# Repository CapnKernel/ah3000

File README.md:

# Raymarine/Nautech Autohelm 3000 control board

Here is a KiCad project of the schematic and layout of the Raymarine/Nautech
Autohelm 3000 control board, a late 80s/early 90s autohelm for sailboats.

These designs were captured by analysing some Autohelm 3000 boards with a
magnifying glass and a multimeter set to the "beep" continuity mode.

There are errors, use with caution.  Component sizes and positions are only approximate.

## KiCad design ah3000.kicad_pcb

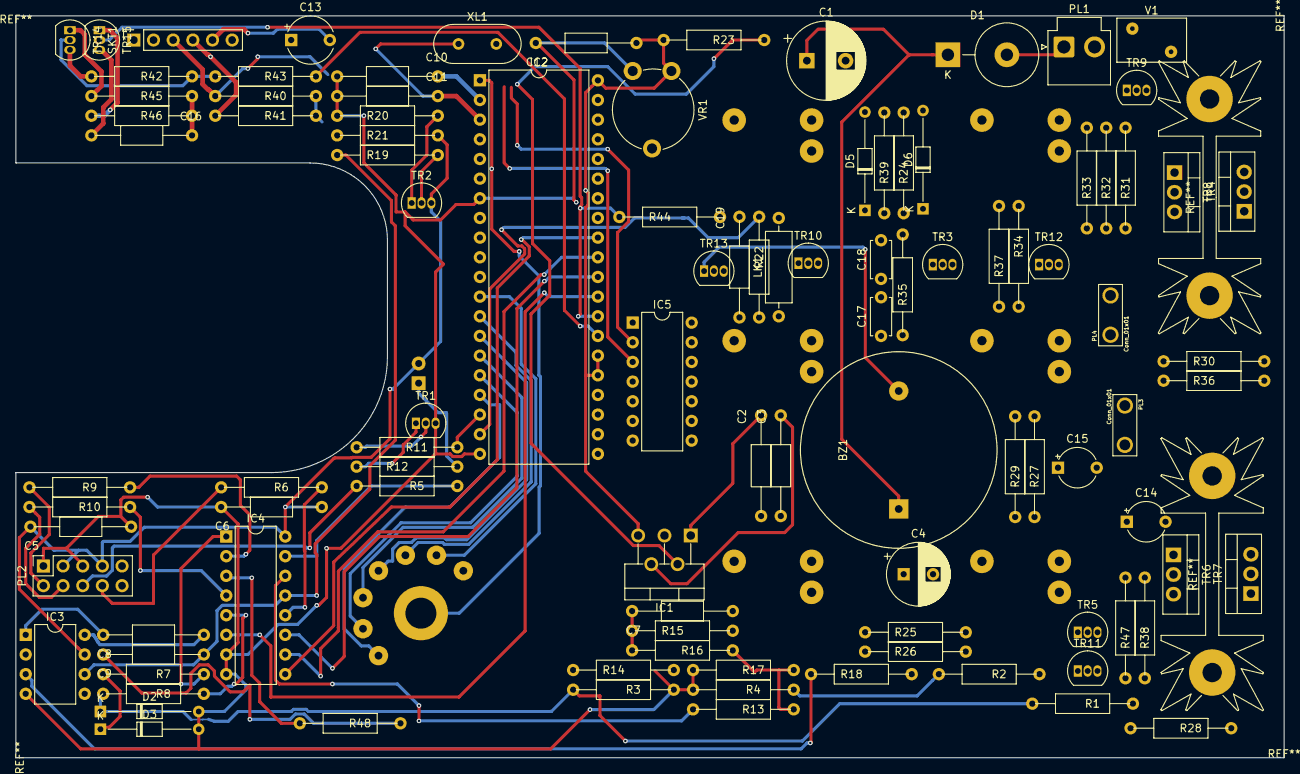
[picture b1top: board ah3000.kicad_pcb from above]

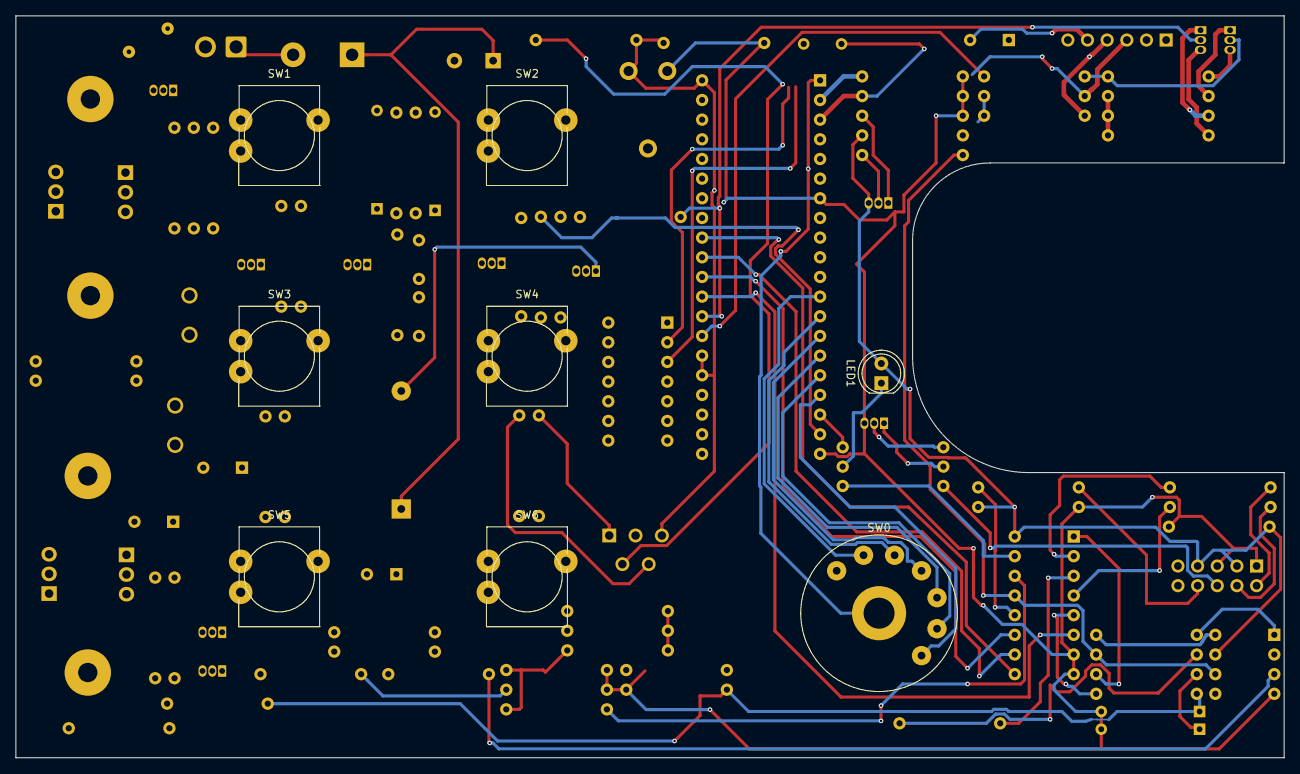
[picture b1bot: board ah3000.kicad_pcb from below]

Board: 2 copper layers, 163.8 x 95.8 mm, 110 parts (8 on the bottom side), 88 nets.

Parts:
BZ1: Buzzer; Buzzer_23x20RM15
C1: CP; CP_Radial_D10.0mm_P5.00mm
C2, C3, C5, C6, C7, C8, C9, C10, C11, C12, C16, C19: C; C_DO-41_SOD81_P12.70mm_Horizontal
C4: CP; CP_Radial_D8.0mm_P3.80mm
C13: 2u2; CP_Radial_Tantal_D6.0mm_P5.00mm
C14, C15: CP; CP_Radial_Tantal_D5.0mm_P5.00mm
C17, C18: C; C_Disc_D4.7mm_W2.5mm_P5.00mm
D1: D; D_5KPW_P7.62mm_Vertical_KathodeUp
D2, D3, D5, D6: D_ALT; D_DO-34_SOD68_P12.70mm_Horizontal
IC1: L487; TO-220-5_P3.4x3.7mm_StaggerOdd_Lead3.8mm_Vertical
IC2: Conn_02x20_Counter_Clockwise; DIP-40_W15.24mm
IC3: CA3130; DIP-8_W7.62mm
IC4: 4051; DIP-16_W7.62mm
IC5: M74HC4066B1R; DIP-14_W7.62mm
LED1: LED_ALT; LED_D5.0mm
LK1: Jumper_NC_Small; R_Axial_DIN0309_L9.0mm_D3.2mm_P12.70mm_Horizontal
PL1: Conn_01x02; JST_VH_B2P-VH-B_1x02_P3.96mm_Vertical
PL2: Conn_02x05_Counter_Clockwise; PinSocket_2x05_P2.54mm_Vertical
PL3, PL4: Conn_01x01; CONN_63824-1
R1, R2, R3, R4, R5, R6, R7, R8, R9, R10, R11, R12, R13, R14, R15, R16, R17, R18, R19, R20, R21, R22, R23, R24, R25, R26, R27, R28, R29, R30, R31, R32, R33, R34, R35, R36, R37, R38, R39, R42, R43, R44, R46, R47, R48: R; R_Axial_DIN0309_L9.0mm_D3.2mm_P12.70mm_Horizontal_AH
R40, R41: 270; R_Axial_DIN0309_L9.0mm_D3.2mm_P12.70mm_Horizontal_AH
R45: 10; R_Axial_DIN0309_L9.0mm_D3.2mm_P12.70mm_Horizontal_AH
SKT1: Conn_01x06_Female; PinSocket_1x06_P2.54mm_Vertical
SW0: SW_7WAY; AH_7WAY
SW1, SW2, SW3, SW4, SW5, SW6: SW_Push_AH; SW_PUSH-12mm
TR1, TR3, TR10, TR13, TR15: BC337; TO-92_Inline
TR2, TR5, TR9, TR11, TR12, TR14: BC327; TO-92_Inline
TR4, TR7: BDW93B; TO-220-3_Vertical
TR6, TR8: BDW94B; TO-220-3_Vertical
V1: Varistor; RV_Disc_D9mm_W5.7mm_P5mm
VR1: 22k; Potentiometer_Piher_PT-10-V10_Vertical
XL1: Crystal_Small; Crystal_HC49-U_Vertical

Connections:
+12V: BZ1.1, C1.1, D1.1, R26.2, R27.2, R32.1, R33.2, R34.2, R47.2, TR6.3, TR8.3, TR11.3, TR12.3
+BATT: C2.2, D1.2, IC1.1, PL1.1
/KP_COL_1: IC2.35, SW1.3, SW3.3, SW5.3
/KP_COL_2: IC2.24, SW2.2, SW4.2, SW6.2
/KP_ROW_1: IC2.21, SW1.2, SW2.3
/KP_ROW_2: IC2.22, SW3.2, SW4.3
/KP_ROW_3: IC2.23, SW5.2, SW6.3
GND: C1.2, C2.1, C3.1, C4.2, C5.1, C6.2, C7.1, C10.1, C11.1, C12.2, C16.1, C17.2, C18.2, C19.2, D2.2, D3.2, IC1.3, IC2.7, IC2.20, IC3.4, IC4.7, IC4.8, IC5.6, IC5.7, IC5.12, LK1.2, PL1.2, PL2.1, PL2.3, R3.1, R4.2, R17.2, R20.1, R31.1, R38.1, SKT1.6, TR1.3, TR3.3, TR4.3, TR7.3, TR10.3, TR13.3, TR15.3, V1.2, VR1.1
unnamed: BZ1.2, TR13.1
unnamed: C3.2, IC1.4
unnamed: C7.2, R15.1, R16.2, R18.2, R40.1, R41.1, SKT1.2
unnamed: C8.1, IC3.8
unnamed: C8.2, IC3.1
unnamed: C9.1, IC3.6, IC4.13, R19.1
unnamed: C9.2, IC3.2, R14.2, R48.1
unnamed: C10.2, IC2.2, XL1.2
unnamed: C11.2, IC2.3, XL1.1
unnamed: C13.1, C16.2, R45.1, R46.1
unnamed: C13.2, SKT1.5
unnamed: C14.1, PL3.1, R1.1, R28.2, TR6.2, TR7.2
unnamed: C14.2, C15.2
unnamed: C15.1, PL4.1, R2.1, R28.1, TR4.2, TR8.2
unnamed: C17.1, D5.2, R29.1
unnamed: C18.1, D6.2, R35.1
unnamed: D2.1, R1.2, R3.2, R8.2
unnamed: D3.1, R2.2, R4.1, R7.2
unnamed: D5.1, R37.1, TR10.1
unnamed: D6.1, R25.1, TR3.1
unnamed: IC1.2, IC2.4, R23.1
unnamed: IC2.1, R21.1, SW0.C
unnamed: IC2.6, R20.2, TR2.1
unnamed: IC2.12, SW0.2
unnamed: IC2.13, SW0.3
unnamed: IC2.14, SW0.4
unnamed: IC2.15, SW0.5
unnamed: IC2.16, SW0.6
unnamed: IC2.17, SW0.7
unnamed: IC2.18, R11.1
unnamed: IC2.19, R22.1
unnamed: IC2.27, R43.2
unnamed: IC2.28, R44.1, TR15.2
unnamed: IC2.29, IC4.6
unnamed: IC2.30, IC4.11
unnamed: IC2.31, IC4.10
unnamed: IC2.32, IC4.9
unnamed: IC2.33, IC5.5
unnamed: IC2.34, IC5.13
unnamed: IC2.36, LK1.1
unnamed: IC2.37, R39.1, TR10.2
unnamed: IC2.38, R24.1, TR3.2
unnamed: IC2.39, VR1.2
unnamed: IC3.3, R18.1
unnamed: IC4.1, R7.1
unnamed: IC4.2, R9.1
unnamed: IC4.3, R48.2
unnamed: IC4.4, R10.1
unnamed: IC4.5, R8.1
unnamed: IC4.12, R6.1
unnamed: IC4.14, R13.2
unnamed: IC4.15, R5.1
unnamed: IC5.1, IC5.4, R14.1
unnamed: IC5.2, R41.2, SKT1.4
unnamed: IC5.3, R40.2, SKT1.3
unnamed: IC5.8, IC5.9, IC5.10, IC5.11
unnamed: LED1.1, R12.2
unnamed: PL2.7, R6.2
unnamed: PL2.8, R5.2
unnamed: PL2.9, R10.2
unnamed: PL2.10, R9.2
unnamed: R11.2, TR1.2
unnamed: R12.1, TR1.1
unnamed: R13.1, R16.1, R17.1
unnamed: R19.2, TR2.2
unnamed: R22.2, TR13.2
unnamed: R25.2, R26.1, TR5.2
unnamed: R27.1, R29.2, TR11.2
unnamed: R30.1, R31.2, TR4.1
unnamed: R30.2, TR5.1
unnamed: R32.2, TR8.1, TR9.3, TR12.1
unnamed: R33.1, R35.2, TR12.2
unnamed: R34.1, R37.2, TR9.2
unnamed: R36.1, R38.2, TR7.1
unnamed: R36.2, TR9.1
unnamed: R42.1, R43.1, TR14.2
unnamed: R45.2, TR14.1
unnamed: R46.2, TR15.1
unnamed: R47.1, TR5.3, TR6.1, TR11.1
VDD: C4.1, C5.2, C6.1, C12.1, C19.1, IC1.5, IC2.25, IC2.26, IC2.40, IC3.7, IC4.16, IC5.14, LED1.2, PL2.2, PL2.4, R15.2, R21.2, R23.2, R24.2, R39.2, R42.2, R44.2, TR2.3, TR14.3, V1.1, VR1.3

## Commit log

2018-12-18 First cut of the schematic
2019-01-04 Lots more improvements, including an early board layout
2019-01-04 Set paper size to A3, and adjusted schematic to fit. Added PDF.
